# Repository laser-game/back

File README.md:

# Back
PCB includes battery monitoring, booster and indication.

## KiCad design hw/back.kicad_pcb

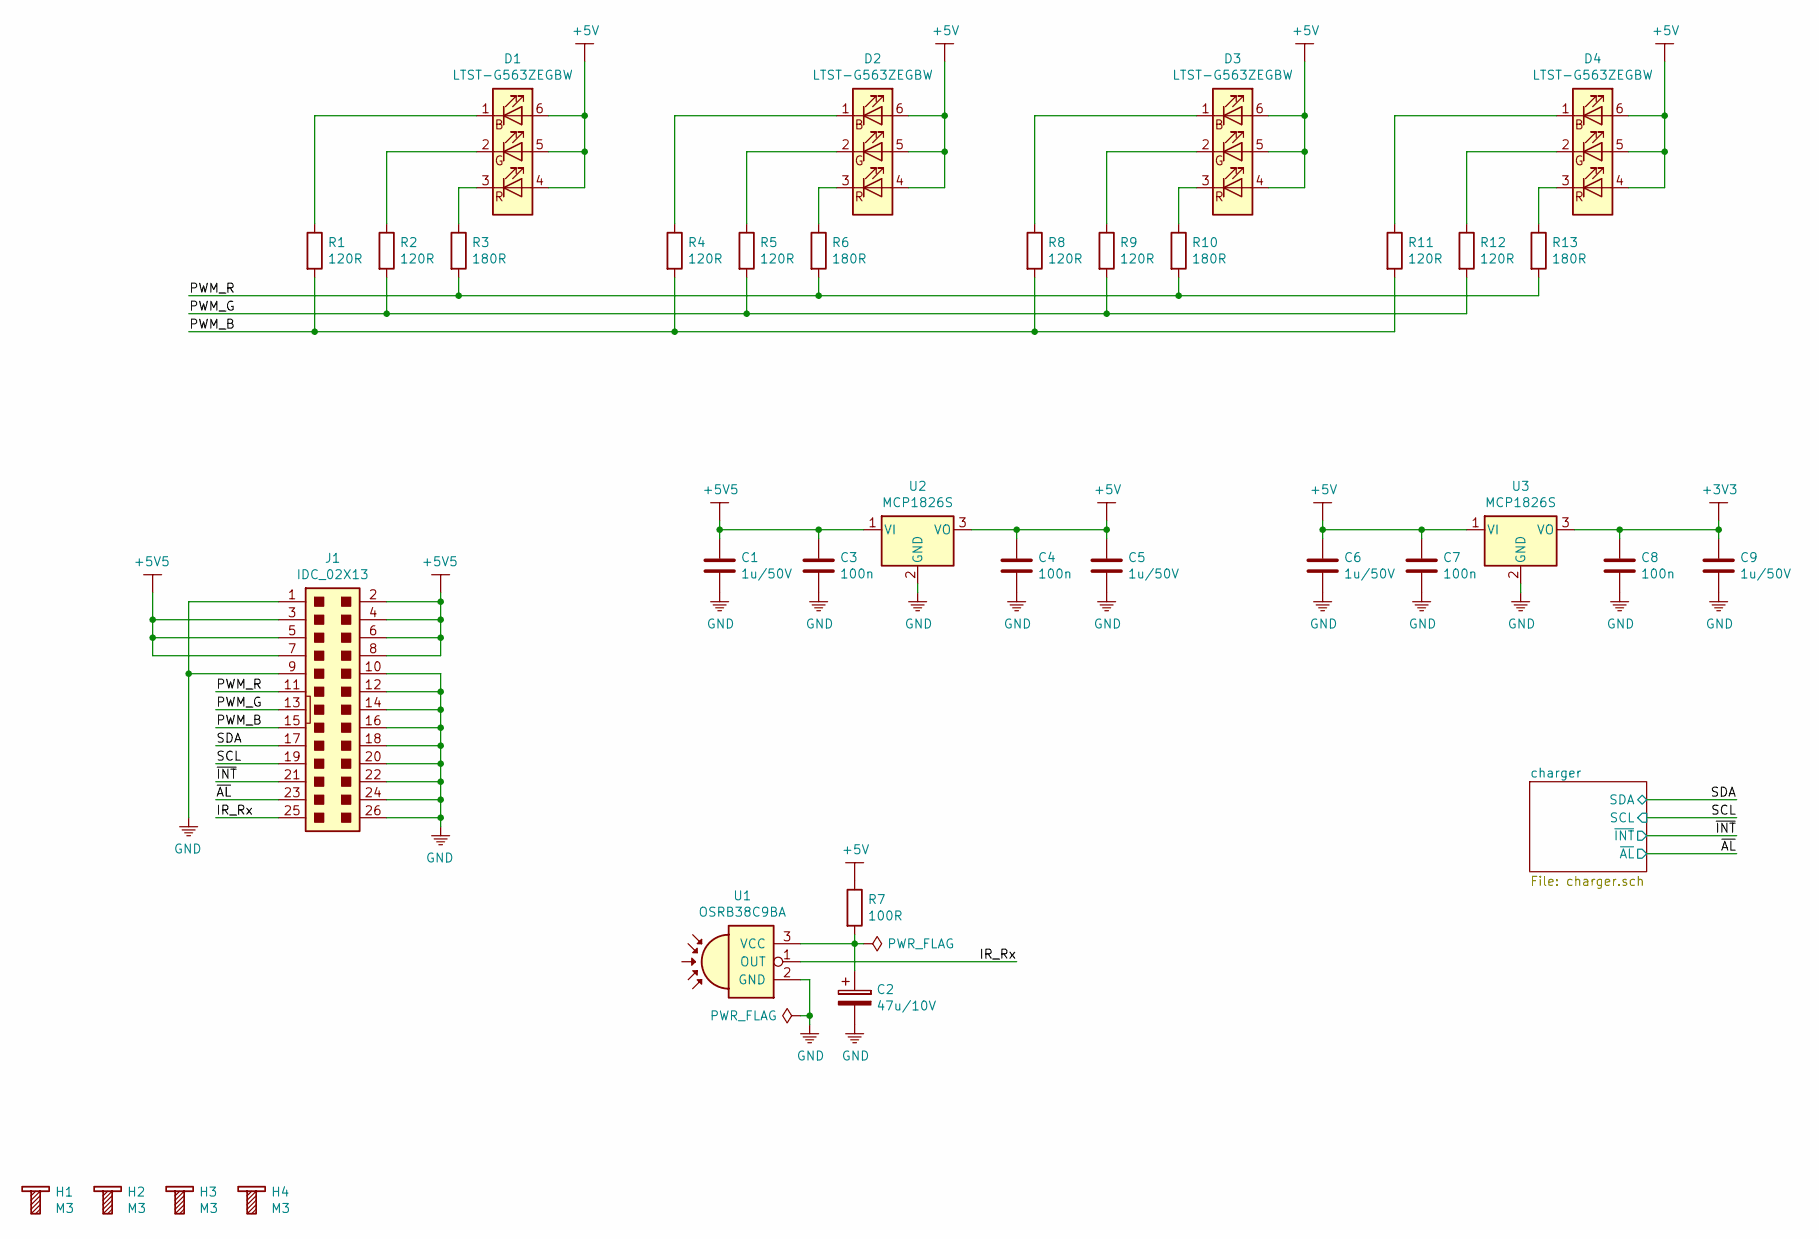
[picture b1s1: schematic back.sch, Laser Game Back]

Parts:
C1, C5, C6, C9: 1u/50V; C_0805_2012Metric
C2: 47u/10V; CP_EIA-3528-21_Kemet-B
C3, C4, C7, C8: 100n; C_0805_2012Metric
D1, D2, D3, D4: LTST-G563ZEGBW; LED_RGB_5050-6
H1, H2, H3, H4: M3; Bolt_M3
J1: IDC_02X13; IDC-Header_2x13_P2.54mm_Vertical
R1, R2, R4, R5, R8, R9, R11, R12: 120R; R_0805_2012Metric
R3, R6, R10, R13: 180R; R_0805_2012Metric
R7: 100R; R_0805_2012Metric
U1: OSRB38C9BA; OSRB8C9BA_Horizontal
U2, U3: MCP1826S; SOT-223-3_TabPin2

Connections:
+3V3: C8.1, C9.1, U3.3 (VO); also elsewhere on the board
+5V: C4.1, C5.1, C6.1, C7.1, D1.4 (BA), D1.5 (GA), D1.6 (RA), D2.4 (BA), D2.5 (GA), D2.6 (RA), D3.4 (BA), D3.5 (GA), D3.6 (RA), D4.4 (BA), D4.5 (GA), D4.6 (RA), R7.1, U2.3 (VO), U3.1 (VI)
+5V5: C1.1, C3.1, J1.2, J1.3, J1.4, J1.5, J1.6, J1.7, J1.8, U2.1 (VI); also elsewhere on the board
/IR_Rx: J1.25, U1.1 (OUT)
/PWM_B: J1.15, R1.2, R4.2, R8.2, R11.2
/PWM_G: J1.13, R2.2, R5.2, R9.2, R12.2
/PWM_R: J1.11, R3.2, R6.2, R10.2, R13.2
/SCL: J1.19; also elsewhere on the board
/SDA: J1.17; also elsewhere on the board
/~AL: J1.23; also elsewhere on the board
/~INT: J1.21; also elsewhere on the board
GND: C1.2, C2.2, C3.2, C4.2, C5.2, C6.2, C7.2, C8.2, C9.2, J1.1, J1.9, J1.10, J1.12, J1.14, J1.16, J1.18, J1.20, J1.22, J1.24, J1.26, U1.2 (GND), U2.2 (GND), U3.2 (GND); also elsewhere on the board
unnamed: C2.1, R7.2, U1.3 (VCC)
unnamed: D1.1 (RK), R1.1
unnamed: D1.2 (GK), R2.1
unnamed: D1.3 (BK), R3.1
unnamed: D2.1 (RK), R4.1
unnamed: D2.2 (GK), R5.1
unnamed: D2.3 (BK), R6.1
unnamed: D3.1 (RK), R8.1
unnamed: D3.2 (GK), R9.1
unnamed: D3.3 (BK), R10.1
unnamed: D4.1 (RK), R11.1
unnamed: D4.2 (GK), R12.1
unnamed: D4.3 (BK), R13.1

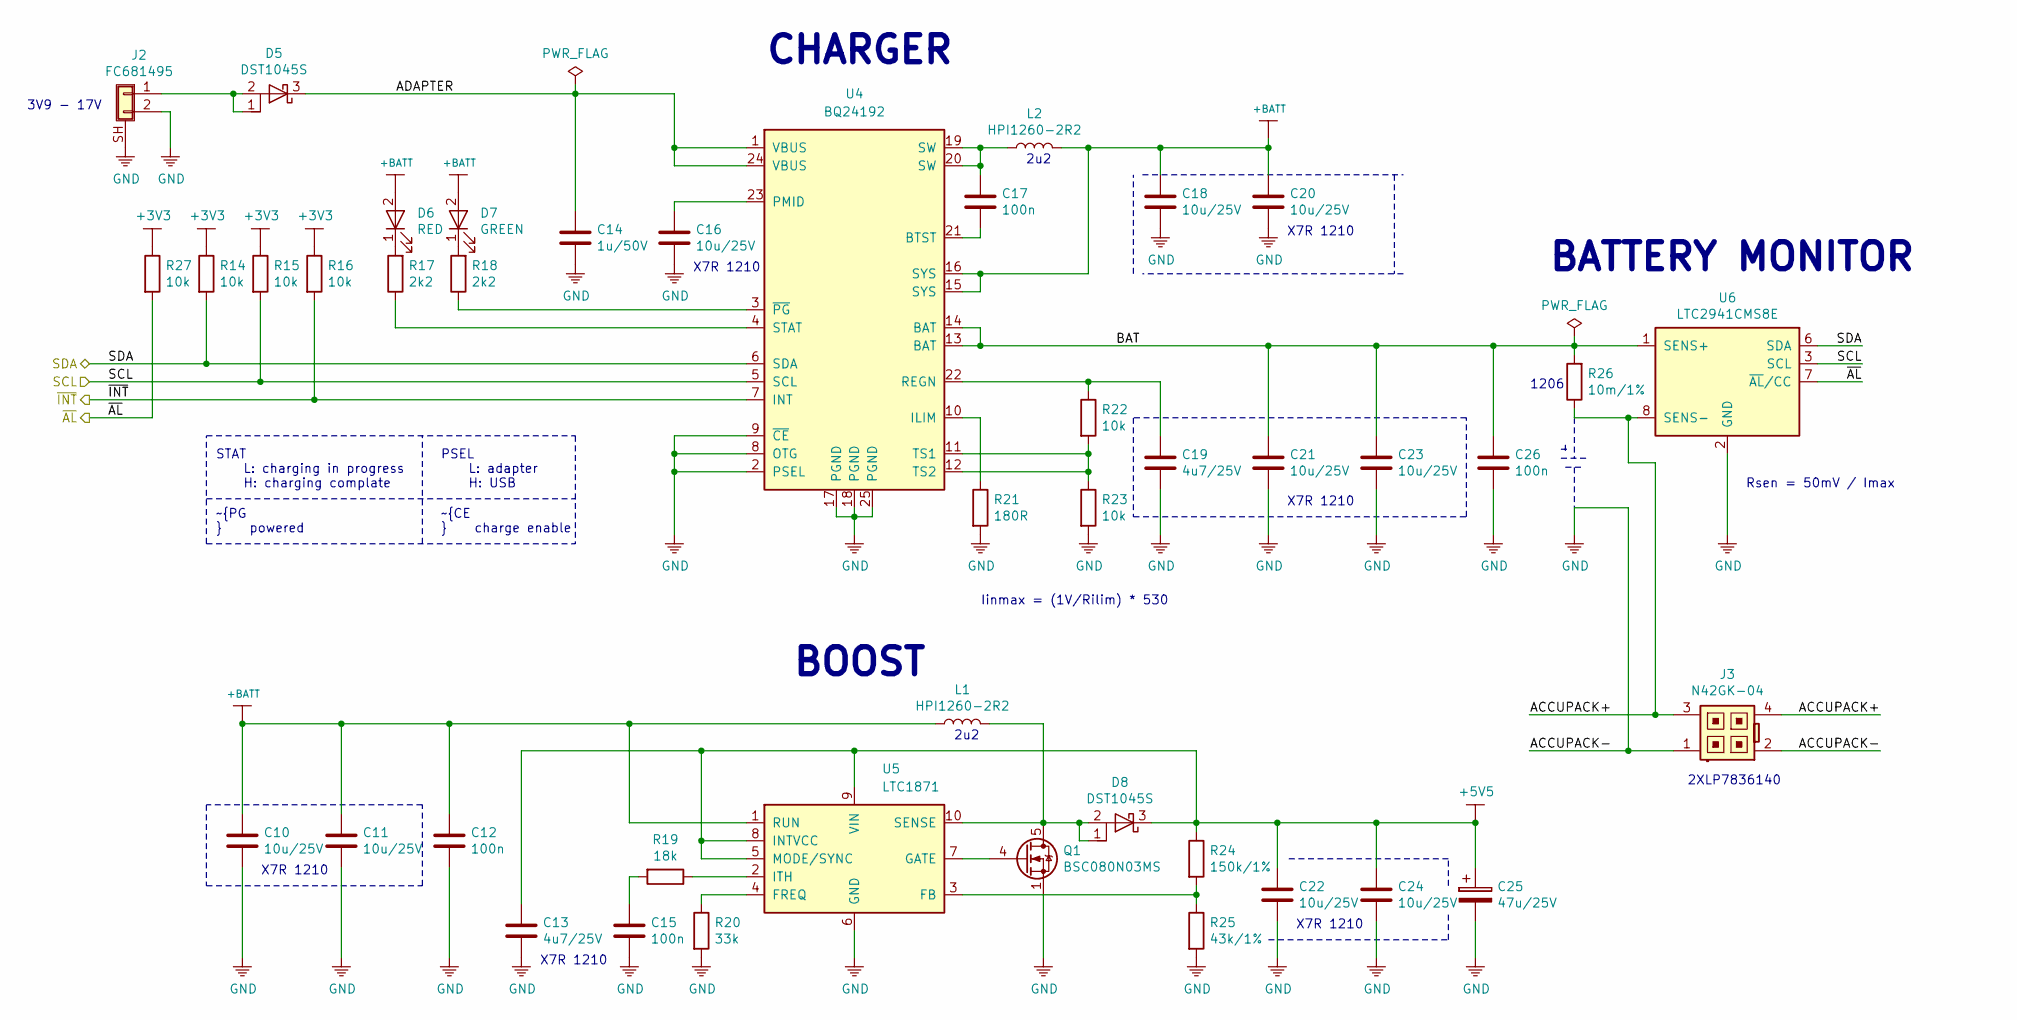
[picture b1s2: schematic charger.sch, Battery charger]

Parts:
C10, C11, C16, C18, C20, C21, C22, C23, C24: 10u/25V; C_1210_3225Metric
C12, C15, C17, C26: 100n; C_0805_2012Metric
C13, C19: 4u7/25V; C_1206_3216Metric
C14: 1u/50V; C_0805_2012Metric
C25: 47u/25V; CP_EIA-7343-31_Kemet-D
D5, D8: DST1045S; TO-277B
D6: RED; LED_0805_2012Metric
D7: GREEN; LED_0805_2012Metric
J2: FC681495; Cliff_FC681495
J3: N42GK-04
L1, L2: HPI1260-2R2; L_12x12mm_H4.5mm
Q1: BSC080N03MS; TDSON-8-1
R14, R15, R16, R22, R23, R27: 10k; R_0805_2012Metric
R17, R18: 2k2; R_0805_2012Metric
R19: 18k; R_0805_2012Metric
R20: 33k; R_0805_2012Metric
R21: 180R; R_0805_2012Metric
R24: 150k/1%; R_0805_2012Metric
R25: 43k/1%; R_0805_2012Metric
R26: 10m/1%; R_1206_3216Metric
U4: BQ24192; QFN-24-1EP_4x4mm_P0.5mm_EP2.6x2.6mm
U5: LTC1871; MSOP-10_3x3mm_P0.5mm
U6: LTC2941CMS8E; MSOP-8-1EP_3x3mm_P0.65mm_EP1.68x1.88mm

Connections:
+3V3: R14.1, R15.1, R16.1, R27.1; also elsewhere on the board
+5V5: C13.1, C22.1, C24.1, C25.1, D8.3 (K), R24.1, U5.5 (MODE/SYNC), U5.8 (INTVCC), U5.9 (VIN); also elsewhere on the board
+BATT: C10.1, C11.1, C12.1, C18.1, C20.1, D6.2 (A), D7.2 (A), L1.1, L2.2, U4.15 (SYS), U4.16 (SYS), U5.1 (RUN)
/SCL: R15.2, U4.5 (SCL), U6.3 (SCL); also elsewhere on the board
/SDA: R14.2, U4.6 (SDA), U6.6 (SDA); also elsewhere on the board
/charger/ACCUPACK+: J3.3, J3.4, R26.1, U6.8 (SENS-)
/charger/ADAPTER: C14.1, D5.3 (K), U4.1 (VBUS), U4.24 (VBUS)
/charger/BAT: C21.1, C23.1, C26.1, R26.2, U4.13 (BAT), U4.14 (BAT), U6.1 (SENS+)
/~AL: R27.2, U6.7 (~AL~/CC); also elsewhere on the board
/~INT: R16.2, U4.7 (INT); also elsewhere on the board
GND: C10.2, C11.2, C12.2, C13.2, C14.2, C15.2, C16.2, C18.2, C19.2, C20.2, C21.2, C22.2, C23.2, C24.2, C25.2, C26.2, J2.2, J2.SH (Shield), J3.1, J3.2, Q1.1 (S), Q1.2 (S), Q1.3 (S), R20.2, R21.2, R23.2, R25.2, U4.2 (PSEL), U4.8 (OTG), U4.9 (~CE), U4.17 (PGND), U4.18 (PGND), U4.25 (PGND), U5.6 (GND), U6.2 (GND); also elsewhere on the board
unnamed: C15.1, R19.2
unnamed: C16.1, U4.23 (PMID)
unnamed: C17.1, L2.1, U4.19 (SW), U4.20 (SW)
unnamed: C17.2, U4.21 (BTST)
unnamed: C19.1, R22.1, U4.22 (REGN)
unnamed: D5.1 (A), D5.2 (A), J2.1
unnamed: D6.1 (K), R17.2
unnamed: D7.1 (K), R18.2
unnamed: D8.1 (A), D8.2 (A), L1.2, Q1.5 (D), U5.10 (SENSE)
unnamed: Q1.4 (G), U5.7 (GATE)
unnamed: R17.1, U4.4 (STAT)
unnamed: R18.1, U4.3 (~PG)
unnamed: R19.1, U5.2 (ITH)
unnamed: R20.1, U5.4 (FREQ)
unnamed: R21.1, U4.10 (ILIM)
unnamed: R22.2, R23.1, U4.11 (TS1), U4.12 (TS2)
unnamed: R24.2, R25.1, U5.3 (FB)

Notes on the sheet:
~CE charge enable
PSEL L: adapter H: USB
X7R 1210
CHARGER
BATTERY MONITOR
BOOST
2u2
Rsen = 50mV / Imax
Iinmax = (1V/Rilim) * 530
STAT L: charging in progress H: charging complate
~PG powered
3V9 - 17V
1206
2XLP7836140

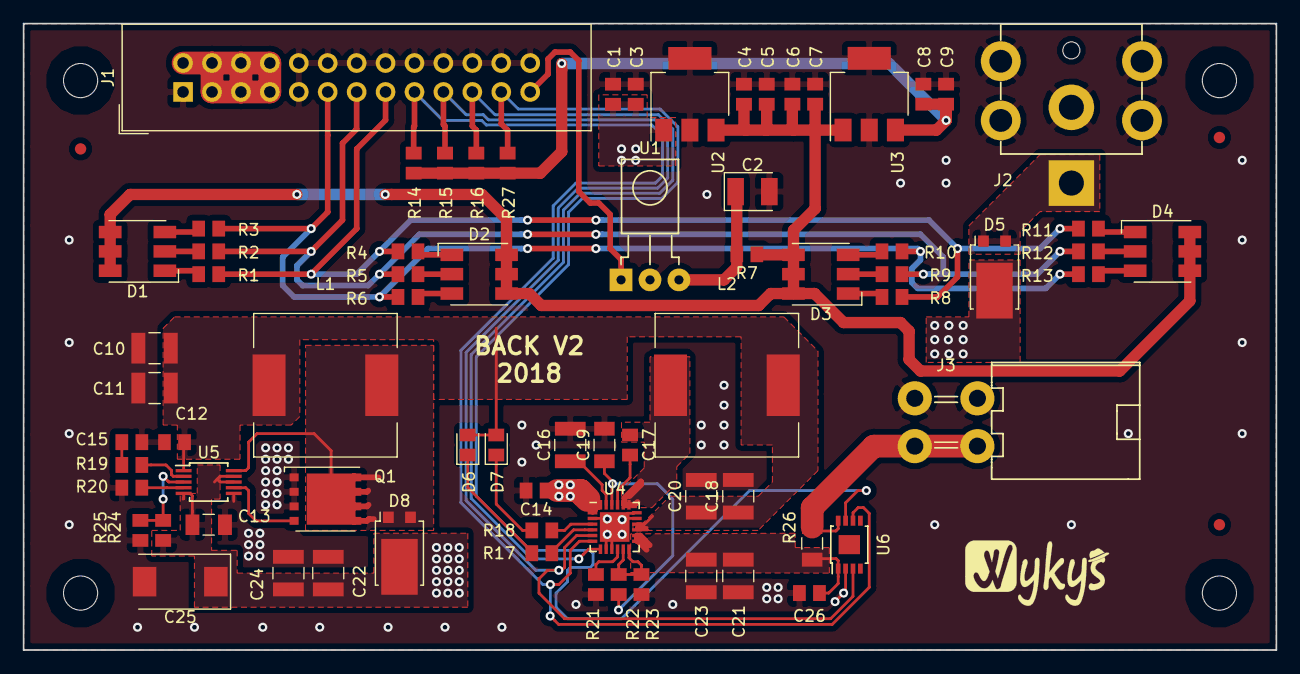
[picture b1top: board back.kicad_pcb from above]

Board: 2 copper layers, 110.0 x 55.0 mm, 77 parts (0 on the bottom side), 46 nets.

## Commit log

2018-03-13 added license
2018-03-13 added .gitignore
2018-03-13 created kicad project
2018-03-21 added first schematic protitype
2018-03-26 updated schematic, select components
2018-03-27 updated schematic, completed charger and created hierarchial list for charger
2018-03-27 moved files
2018-03-28 updated schematic ERC ok
2018-03-28 updated schematic
2018-03-30 added simulation file for boost in lt-spice
2018-03-30 updated .gitignore and readme
2018-03-30 deleted back.net from repository
2018-04-17 updated .gitignore
2018-04-17 updated pcb
2018-04-20 updated C2 footprint
2018-04-20 updated power connector footprint
2018-04-20 chenged pads from thermal to solid in boost
2018-05-02 added boom file and schematic for fabracation
2018-05-08 added placement files

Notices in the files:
README.md:
License: CC BY-NC-ND 4.0
